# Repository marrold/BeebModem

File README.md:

# LeWiFiModem

A WiFi modem that enables retro computers to connect to BBS and Viewdata services over TCP. 

It uses an ESP8266 based Microcontroller running the [ZiModem](https://github.com/bozimmerman/Zimodem) firmware

**Note:** It's currently untested

## License

- This project is licensed under the MIT license
- [ZiModem](https://github.com/bozimmerman/Zimodem) is licensed under the Apache 2.0 license

## FAQ

 - **Why "Le WiFi Modem"?**
	 [Le Modem](https://www.computinghistory.org.uk/det/38081/Watford-Electronics-Le-Modem/) was the name of a modem manufactured by Watford Electronics in the mid-eighties.

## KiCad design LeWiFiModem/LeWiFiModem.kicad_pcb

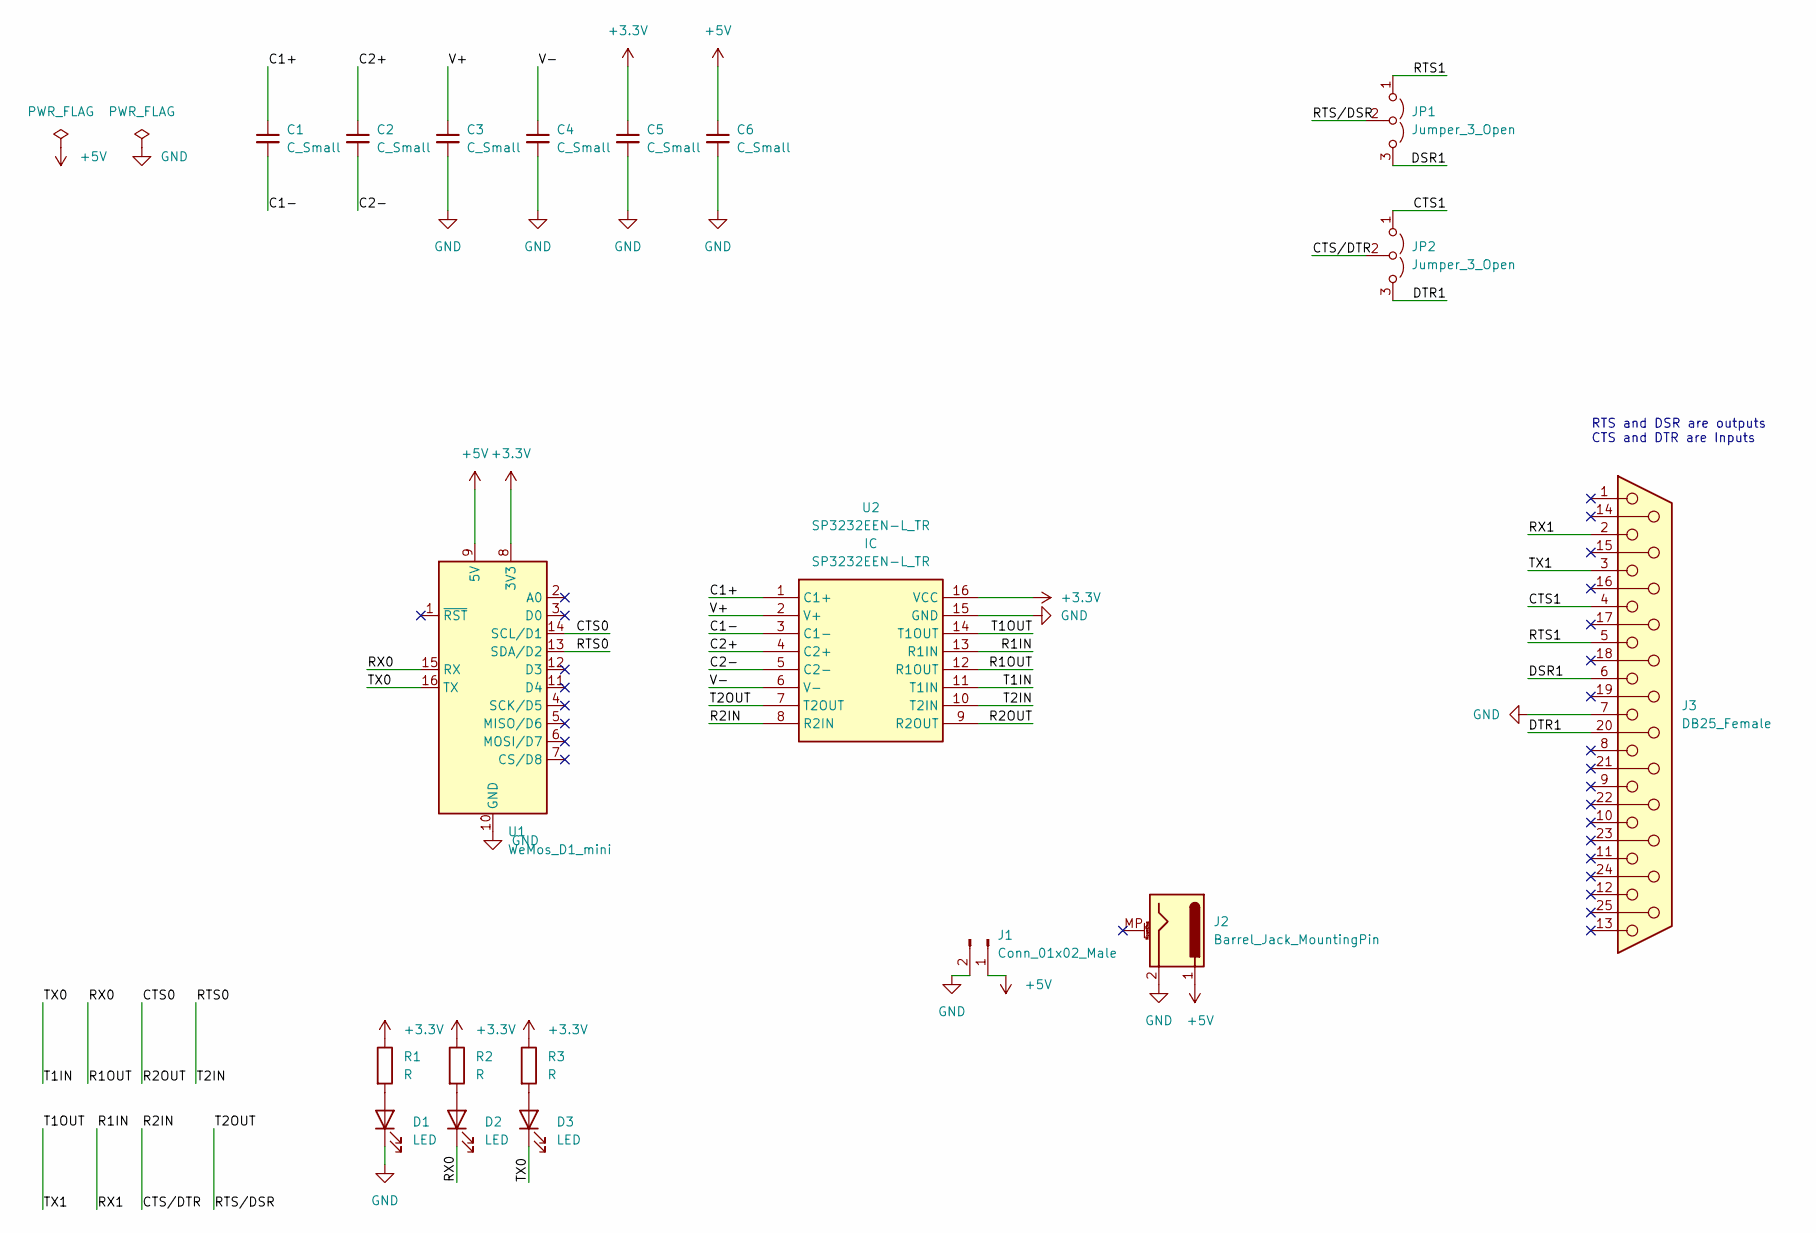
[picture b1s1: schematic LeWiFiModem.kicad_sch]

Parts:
C1, C2, C3, C4, C5: C_Small; C_0805_2012Metric
C6: C_Small; CP_Radial_D5.0mm_P2.00mm
D1, D2, D3: LED; LED_0805_2012Metric
J1: Conn_01x02_Male; PinHeader_1x02_P2.54mm_Vertical
J2: Barrel_Jack_MountingPin; BarrelJack_Horizontal
J3: DB25_Female; DSUB-25_Female_Horizontal_P2.77x2.84mm_EdgePinOffset7.70mm_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
JP1, JP2: Jumper_3_Open; PinHeader_1x03_P2.54mm_Vertical
R1, R2, R3: R; R_0805_2012Metric
U1: WeMos_D1_mini; WEMOS_D1_mini_light
U2: SP3232EEN-L_TR; SOIC127P600X175-16N; Mouser Part Number 701-SP3232EEN-L/TR

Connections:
+3.3V: C5.1, R1.1, R2.1, R3.1, U1.8 (3V3), U2.16 (VCC)
+5V: C6.1, J1.1, J2.1, U1.9 (5V)
/C1+: C1.1, U2.1 (C1+)
/C1-: C1.2, U2.3 (C1-)
/C2+: C2.1, U2.4 (C2+)
/C2-: C2.2, U2.5 (C2-)
/CTS0: U1.14 (SCL/D1), U2.9 (R2OUT)
/CTS1: J3.4, JP2.1 (A)
/CTS/DTR: JP2.2 (C), U2.8 (R2IN)
/DSR1: J3.6, JP1.3 (B)
/DTR1: J3.20, JP2.3 (B)
/R1IN: J3.2, U2.13 (R1IN)
/R1OUT: D2.1 (K), U1.15 (RX), U2.12 (R1OUT)
/RTS0: U1.13 (SDA/D2), U2.10 (T2IN)
/RTS1: J3.5, JP1.1 (A)
/RTS/DSR: JP1.2 (C), U2.7 (T2OUT)
/T1IN: D3.1 (K), U1.16 (TX), U2.11 (T1IN)
/T1OUT: J3.3, U2.14 (T1OUT)
/V+: C3.1, U2.2 (V+)
/V-: C4.1, U2.6 (V-)
GND: C3.2, C4.2, C5.2, C6.2, D1.1 (K), J1.2, J2.2, J3.7, U1.10 (GND), U2.15 (GND)
unnamed: D1.2 (A), R1.2
unnamed: D2.2 (A), R2.2
unnamed: D3.2 (A), R3.2

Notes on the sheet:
RTS and DSR are outputs CTS and DTR are Inputs

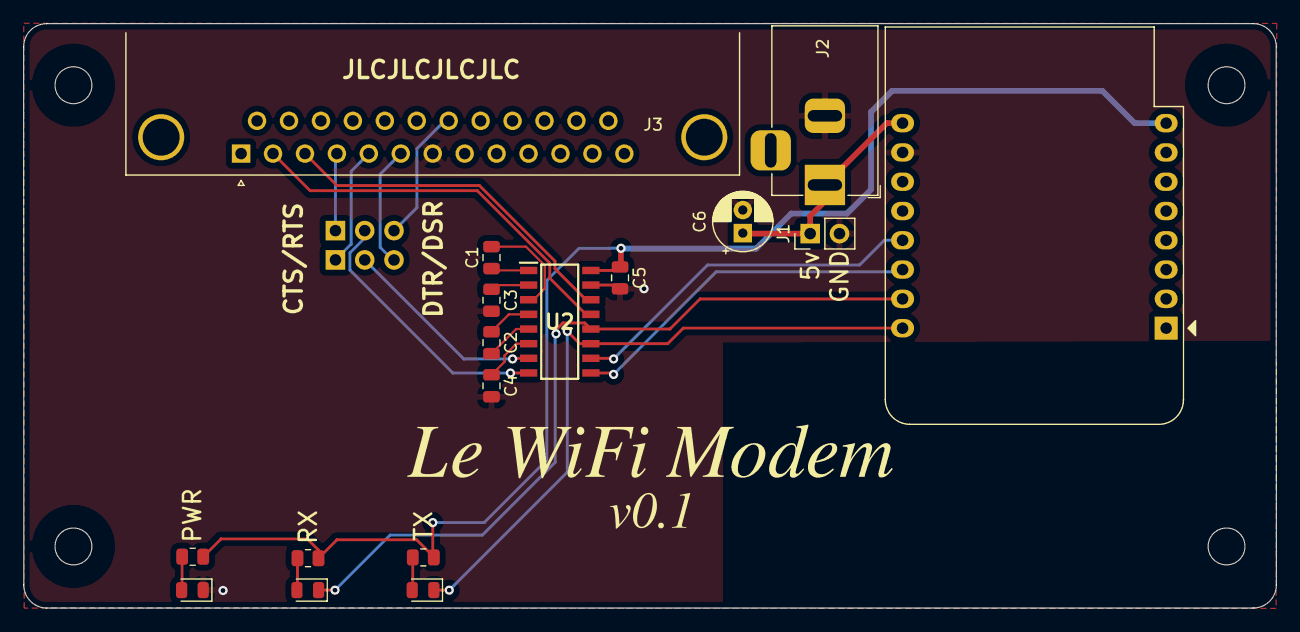
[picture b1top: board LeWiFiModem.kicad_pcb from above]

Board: 2 copper layers, 108.6 x 50.7 mm, 19 parts (0 on the bottom side), 24 nets.

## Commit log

2024-01-03 init
